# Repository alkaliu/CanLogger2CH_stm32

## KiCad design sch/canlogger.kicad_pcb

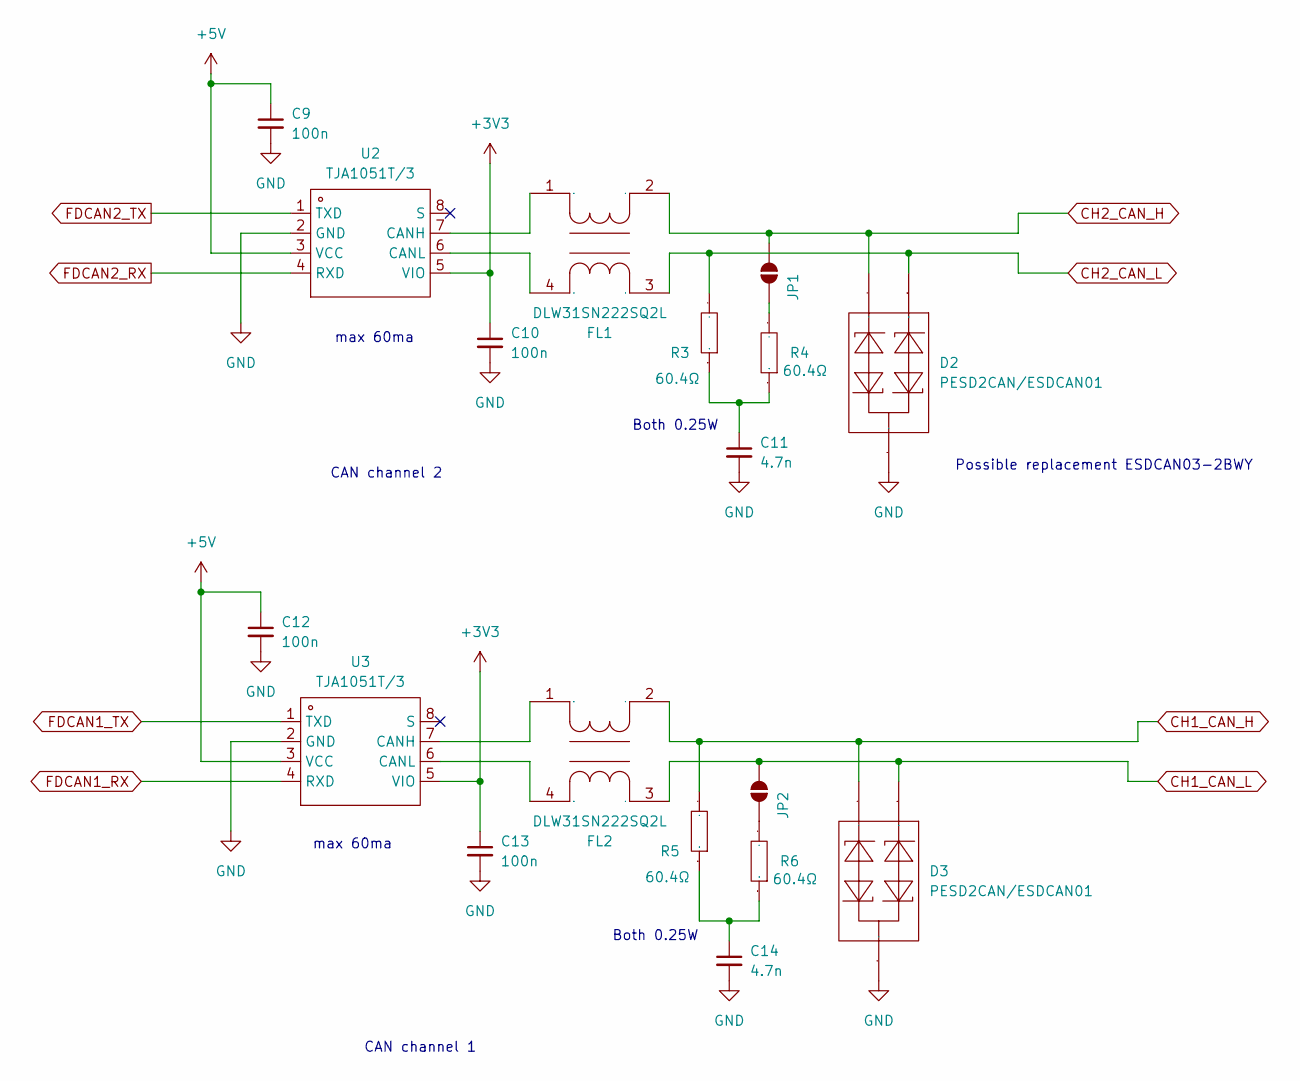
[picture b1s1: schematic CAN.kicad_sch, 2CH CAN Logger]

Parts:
C9, C10, C12, C13: 100n; C0603
C11, C14: 4.7n; C0603
D2, D3: PESD2CAN/ESDCAN01; SOT-23-3_L2.9-W1.3-P1.90-LS2.4-BR; Manufacturer Part PESD2CAN,215; LCSC Part Name 双向ESD 24V截止 峰值脉冲电流：5A@8/20us
FL1, FL2: DLW31SN222SQ2L; FILTER-SMD_4P-L3.2-W1.6-BL_DLW31SN222SQ2L; Manufacturer Part DLW31SN222SQ2L; LCSC Part Name 两路 贴片共模滤波器 阻抗2.2kΩ@100MHz
JP1, JP2: SolderJumper_2_Open; SolderJumper-2_P1.3mm_Open_RoundedPad1.0x1.5mm
R3, R4, R5, R6: 60.4Ω; R1206; Manufacturer Part 1206W4F604JT5E; LCSC Part Name 60.4Ω ±1% 250mW 厚膜电阻
U2, U3: TJA1051T/3; SOIC-8_L4.9-W3.9-P1.27-LS6.0-BL; Manufacturer Part TJA1051T/3/1J; LCSC Part Name TJA1051T/3/1J

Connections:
+3V3: C10.1, C13.1, U2.5 (VIO), U3.5 (VIO); also elsewhere on the board
+5V: C9.1, C12.1, U2.3 (VCC), U3.3 (VCC); also elsewhere on the board
CH1_CAN_H: D3.2, FL2.2, R5.2; also elsewhere on the board
CH1_CAN_L: D3.1, FL2.3, JP2.2 (B); also elsewhere on the board
CH2_CAN_H: D2.2, FL1.2, JP1.2 (B); also elsewhere on the board
CH2_CAN_L: D2.1, FL1.3, R3.2; also elsewhere on the board
FDCAN1_RX: U3.4 (RXD); also elsewhere on the board
FDCAN1_TX: U3.1 (TXD); also elsewhere on the board
FDCAN2_RX: U2.4 (RXD); also elsewhere on the board
FDCAN2_TX: U2.1 (TXD); also elsewhere on the board
GND: C9.2, C10.2, C11.2, C12.2, C13.2, C14.2, D2.3, D3.3, U2.2 (GND), U3.2 (GND); also elsewhere on the board
unnamed: C11.1, R3.1, R4.1
unnamed: C14.1, R5.1, R6.1
unnamed: JP1.1 (A), R4.2
unnamed: JP2.1 (A), R6.2
unnamed: FL1.1, U2.7 (CANH)
unnamed: FL1.4, U2.6 (CANL)
unnamed: FL2.1, U3.7 (CANH)
unnamed: FL2.4, U3.6 (CANL)

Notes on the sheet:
Both 0.25W
max 60ma
CAN channel 2
Possible replacement ESDCAN03-2BWY
CAN channel 1

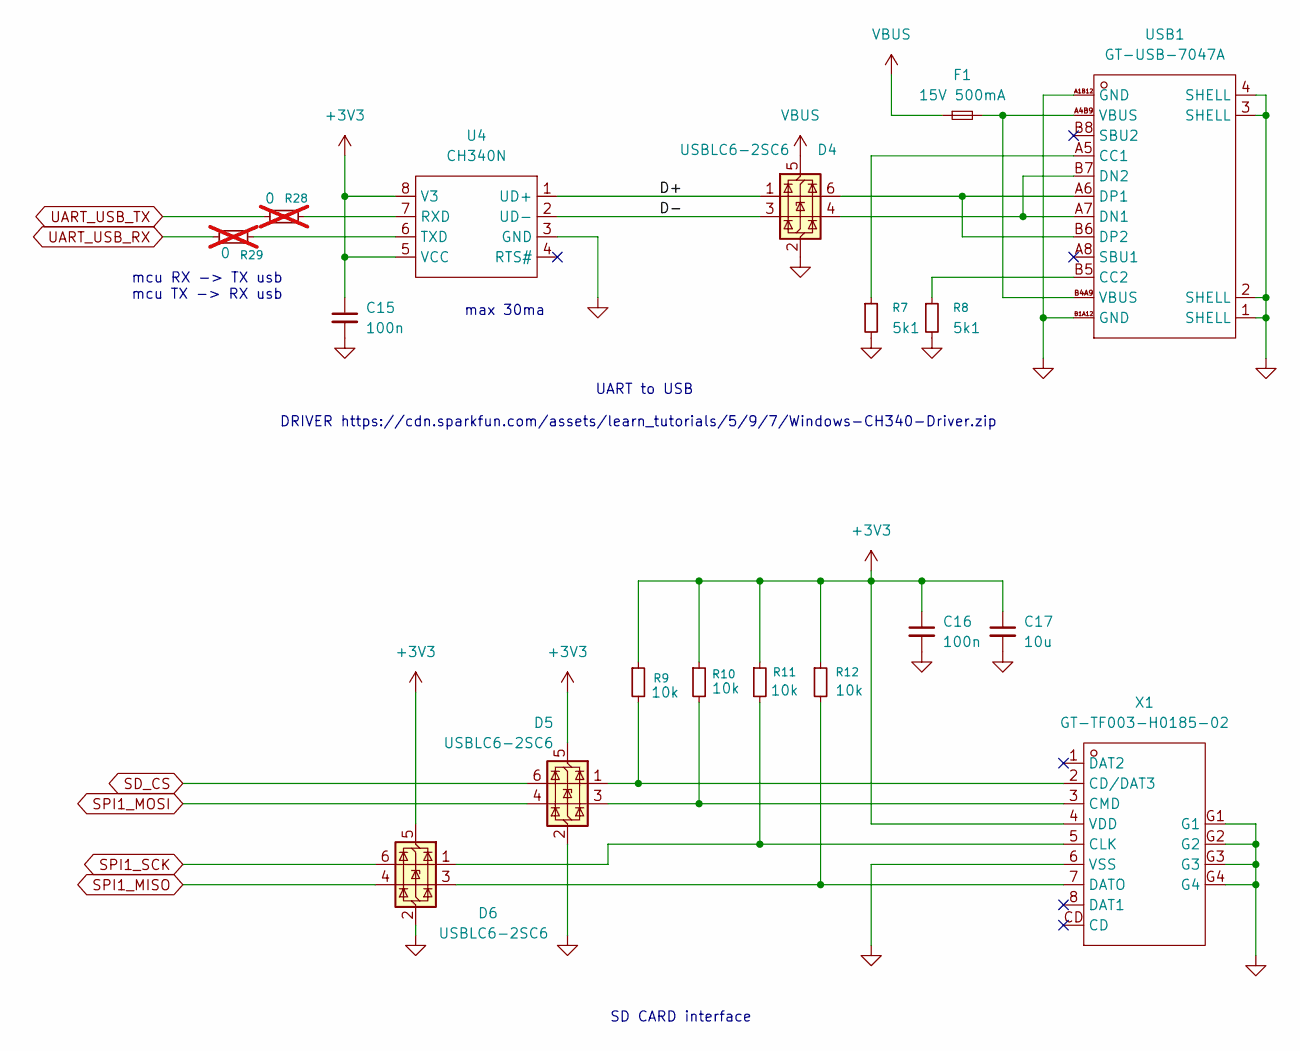
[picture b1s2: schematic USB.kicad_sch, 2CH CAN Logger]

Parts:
C15, C16: 100n; C0603
C17: 10u; C0805
D4, D5, D6: USBLC6-2SC6; SOT-23-6_L2.9-W1.6-P0.95-LS2.8-BL; Manufacturer Part USBLC6-2SC6; LCSC Part Name 单向ESD
F1: 15V 500mA; F1812; Manufacturer Part SMD1812P050TF; LCSC Part Name 15V 500mA 1812自恢复
R7, R8: 5k1; R0603
R9, R10, R11, R12: 10k; R0603
R28, R29: 0; R0603; not fitted
U4: CH340N; SOP-8_L4.9-W3.9-P1.27-LS6.0-BL; Manufacturer Part CH340N; LCSC Part Name USB2.0芯片CH340
USB1: GT-USB-7047A; USB-C-SMD_GT-USB-7047A; Manufacturer Part GT-USB-7047A; LCSC Part Name Type-C 母 卧贴
X1: GT-TF003-H0185-02; SIM-SMD_GT-TF003-H0185-02; Manufacturer Part GT-TF003-H0185-02; LCSC Part Name 自弹式 MicroSD卡(TF卡) 卡座

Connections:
+3V3: C15.1, C16.1, C17.1, D5.5 (VBUS), D6.5 (VBUS), R9.1, R10.1, R11.1, R12.1, U4.5 (VCC), U4.8 (V3), X1.4 (VDD); also elsewhere on the board
/USB_SDCARD/D+: D4.1 (I/O1), U4.1 (UD+)
/USB_SDCARD/D-: D4.3 (I/O2), U4.2 (UD-)
GND: C15.2, C16.2, C17.2, D4.2 (GND), D5.2 (GND), D6.2 (GND), R7.2, R8.2, U4.3 (GND), USB1.1 (SHELL), USB1.2 (SHELL), USB1.3 (SHELL), USB1.4 (SHELL), USB1.A1B12 (GND), USB1.B1A12 (GND), X1.6 (VSS), X1.G1, X1.G2, X1.G3, X1.G4; also elsewhere on the board
unnamed: F1.2, USB1.A4B9 (VBUS), USB1.B4A9 (VBUS)
unnamed: R28.2, U4.7 (RXD)
unnamed: R29.2, U4.6 (TXD)
unnamed: R7.1, USB1.A5 (CC1)
unnamed: R8.1, USB1.B5 (CC2)
unnamed: D4.4 (I/O2), USB1.A7 (DN1), USB1.B7 (DN2)
unnamed: D4.6 (I/O1), USB1.A6 (DP1), USB1.B6 (DP2)
unnamed: D5.1 (I/O1), R9.2, X1.2 (CD/DAT3)
unnamed: D6.1 (I/O1), R11.2, X1.5 (CLK)
unnamed: D5.3 (I/O2), R10.2, X1.3 (CMD)
unnamed: D6.3 (I/O2), R12.2, X1.7 (DATO)
SD_CS: D5.6 (I/O1); also elsewhere on the board
SPI1_MISO: D6.4 (I/O2); also elsewhere on the board
SPI1_MOSI: D5.4 (I/O2); also elsewhere on the board
SPI1_SCK: D6.6 (I/O1); also elsewhere on the board
UART_USB_RX: R29.1; also elsewhere on the board
UART_USB_TX: R28.1; also elsewhere on the board
VBUS: D4.5 (VBUS), F1.1; also elsewhere on the board

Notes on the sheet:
SD CARD interface
DRIVER https://cdn.sparkfun.com/assets/learn_tutorials/5/9/7/Windows-CH340-Driver.zip
max 30ma
mcu RX -> TX usb mcu TX -> RX usb
UART to USB

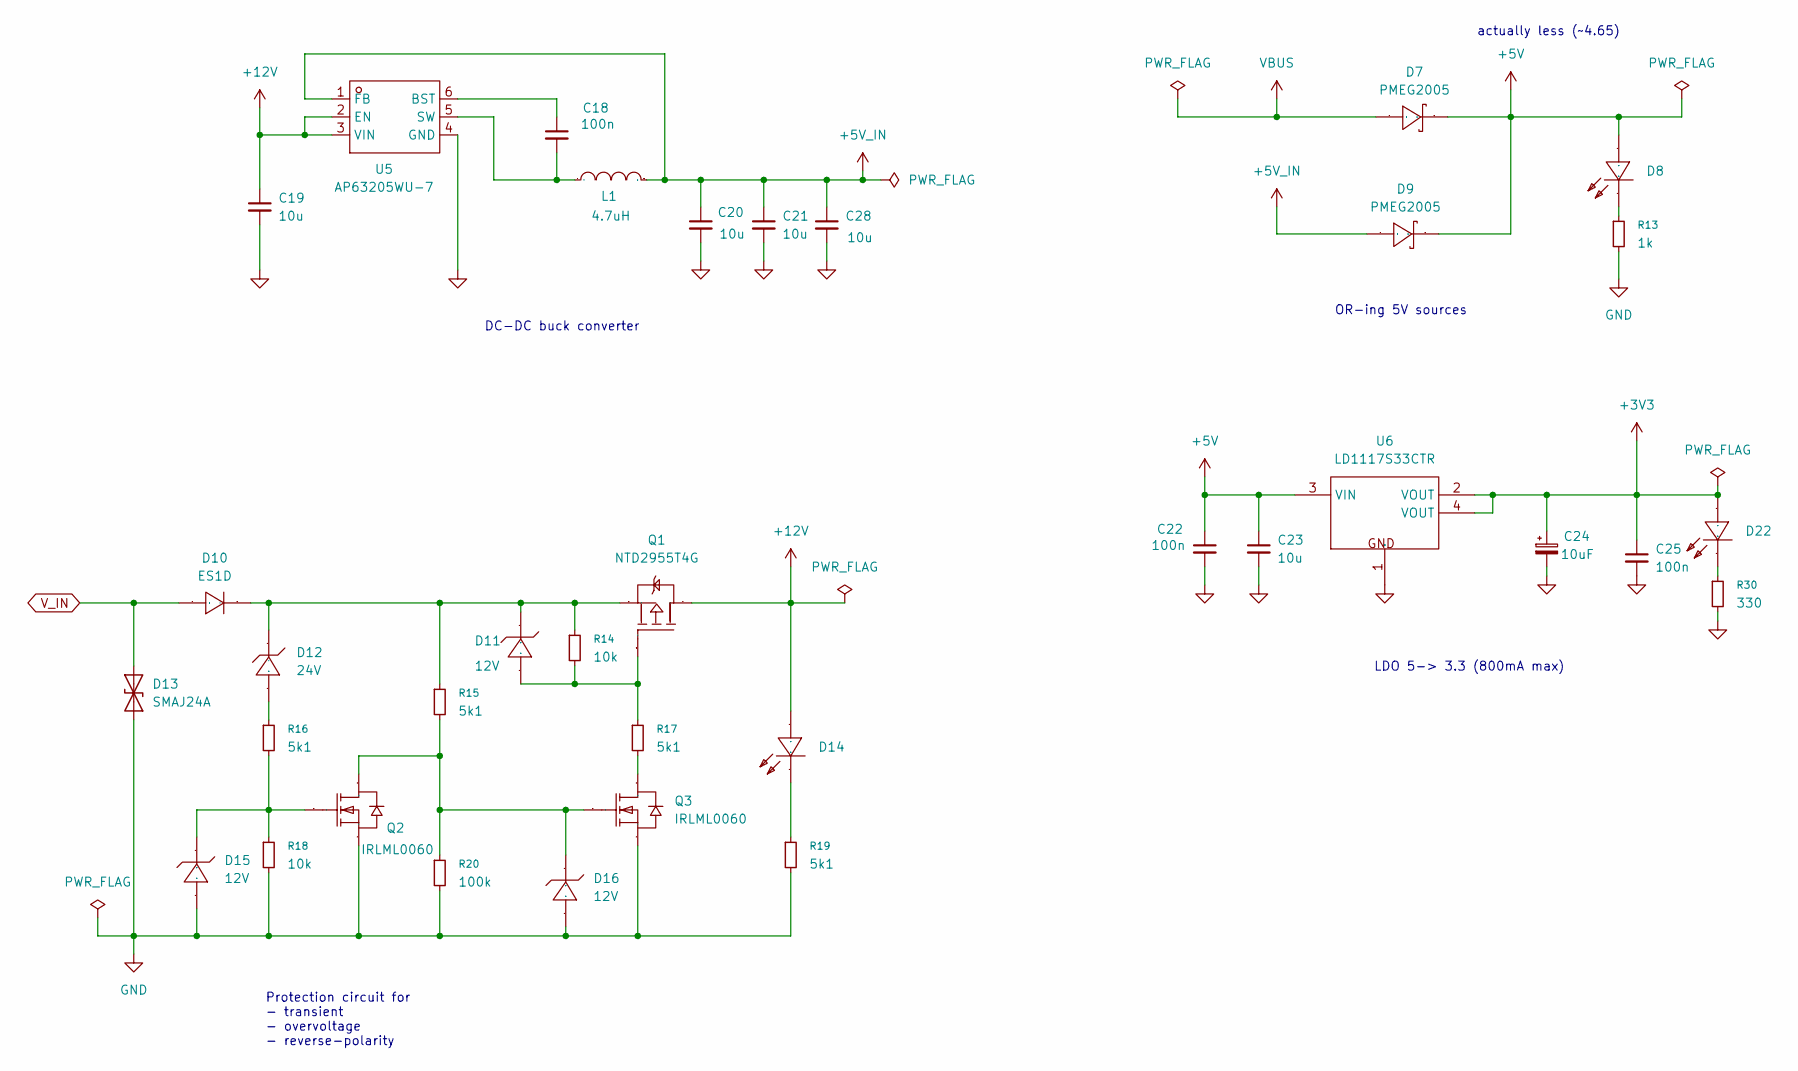
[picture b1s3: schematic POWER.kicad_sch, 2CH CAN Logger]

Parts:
C18, C22, C25: 100n; C0603
C19, C20, C21, C23, C28: 10u; C0805
C24: 10uF; CASE-A_3216; Manufacturer Part TAJA106K010RNJ; LCSC Part Name 10uF ±10% 10V
D7, D9: PMEG2005; SOD-123_L2.8-W1.8-LS3.7-RD; Manufacturer Part PMEG2005EGWX; LCSC Part Name 电压:20V 电流:500mA
D8, D14, D22: LED0603-RD; Manufacturer Part KT-0603R; LCSC Part Name 0603 红灯 高亮
D10: ES1D; SMA_L4.3-W2.6-LS5.2-RD; Manufacturer Part ES1D-E3/61T; LCSC Part Name 耐压:200V 电流:1A 反向恢复时间：15ns
D11, D15, D16: 12V; SOD-123_L2.8-W1.8-LS3.7-RD; Manufacturer Part MMSZ12T1G; LCSC Part Name MMSZ12T1G
D12: 24V; SOD-123_L2.8-W1.8-LS3.7-RD; Manufacturer Part MMSZ5252BT1G; LCSC Part Name MMSZ5252BT1G
D13: SMAJ24A; SMA_L4.4-W2.6-LS5.0-RD; Manufacturer Part SMAJ24A; LCSC Part Name 单向TVS 24V截止 10.3A峰值脉冲
L1: 4.7uH; IND-SMD_L4.4-W4.2-A; Manufacturer Part 0420CDMCCDS-4R7MC; LCSC Part Name 4.7uH ±20% 3A
Q1: NTD2955T4G; TO-252-2_L6.6-W6.1-P4.57-LS9.9-TL-CW; Manufacturer Part NTD2955T4G; LCSC Part Name 1个P沟道 耐压:60V 电流:12A
Q2, Q3: IRLML0060; SOT-23-3_L2.9-W1.6-P1.90-LS2.8-BR; Manufacturer Part IRLML0060TRPBF; LCSC Part Name 1个N沟道 耐压:60V 电流:2.7A
R13: 1k; R0603
R14, R18: 10k; R0603
R15, R16, R17, R19: 5k1; R0603
R20: 100k; R0603
R30: 330; R0603
U5: AP63205WU-7; TSOT-23-6_L2.9-W1.6-P0.95-LS2.8-BL; Manufacturer Part AP63205WU-7; LCSC Part Name 3.8V至32V输入、2A低静态电流同步降压转换器，增强EMI抑制
U6: LD1117S33CTR; SOT-223-4_L6.5-W3.5-P2.30-LS7.0-BR; Manufacturer Part LD1117S33CTR; LCSC Part Name 可调与固定低压降正电压稳压器

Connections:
+3V3: C24.1, C25.1, D22.2 (A), U6.2 (VOUT), U6.4 (VOUT); also elsewhere on the board
+5V: C22.1, C23.1, D7.1 (A), D8.2 (A), D9.1 (A), U6.3 (VIN); also elsewhere on the board
+5V_IN: C20.1, C21.1, C28.1, D9.2 (K), L1.1, U5.1 (FB)
+12V: C19.1, D14.2 (A), Q1.2 (D), U5.2 (EN), U5.3 (VIN)
GND: C19.2, C20.2, C21.2, C22.2, C23.2, C24.2, C25.2, C28.2, D13.2 (A2), D15.2 (A), D16.2 (A), Q2.2 (S), Q3.2 (S), R13.2, R18.2, R19.2, R20.2, R30.2, U5.4 (GND), U6.1 (GND); also elsewhere on the board
unnamed: D8.1 (K), R13.1
unnamed: D10.1 (C), D11.1 (K), D12.1 (C), Q1.3 (S), R14.1, R15.1
unnamed: D11.2 (A), Q1.1 (G), R14.2, R17.1
unnamed: D12.2 (A), R16.1
unnamed: D14.1 (K), R19.1
unnamed: D15.1 (K), Q2.1 (G), R16.2, R18.1
unnamed: D16.1 (K), Q2.3 (D), Q3.1 (G), R15.2, R20.1
unnamed: D22.1 (K), R30.1
unnamed: Q3.3 (D), R17.2
unnamed: C18.1, U5.6 (BST)
unnamed: C18.2, L1.2, U5.5 (SW)
VBUS: D7.2 (K); also elsewhere on the board
V_IN: D10.2 (A), D13.1 (A1); also elsewhere on the board

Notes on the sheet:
LDO 5-> 3.3 (800mA max)
OR-ing 5V sources
DC-DC buck converter
actually less (~4.65)
Protection circuit for - transient - overvoltage - reverse-polarity

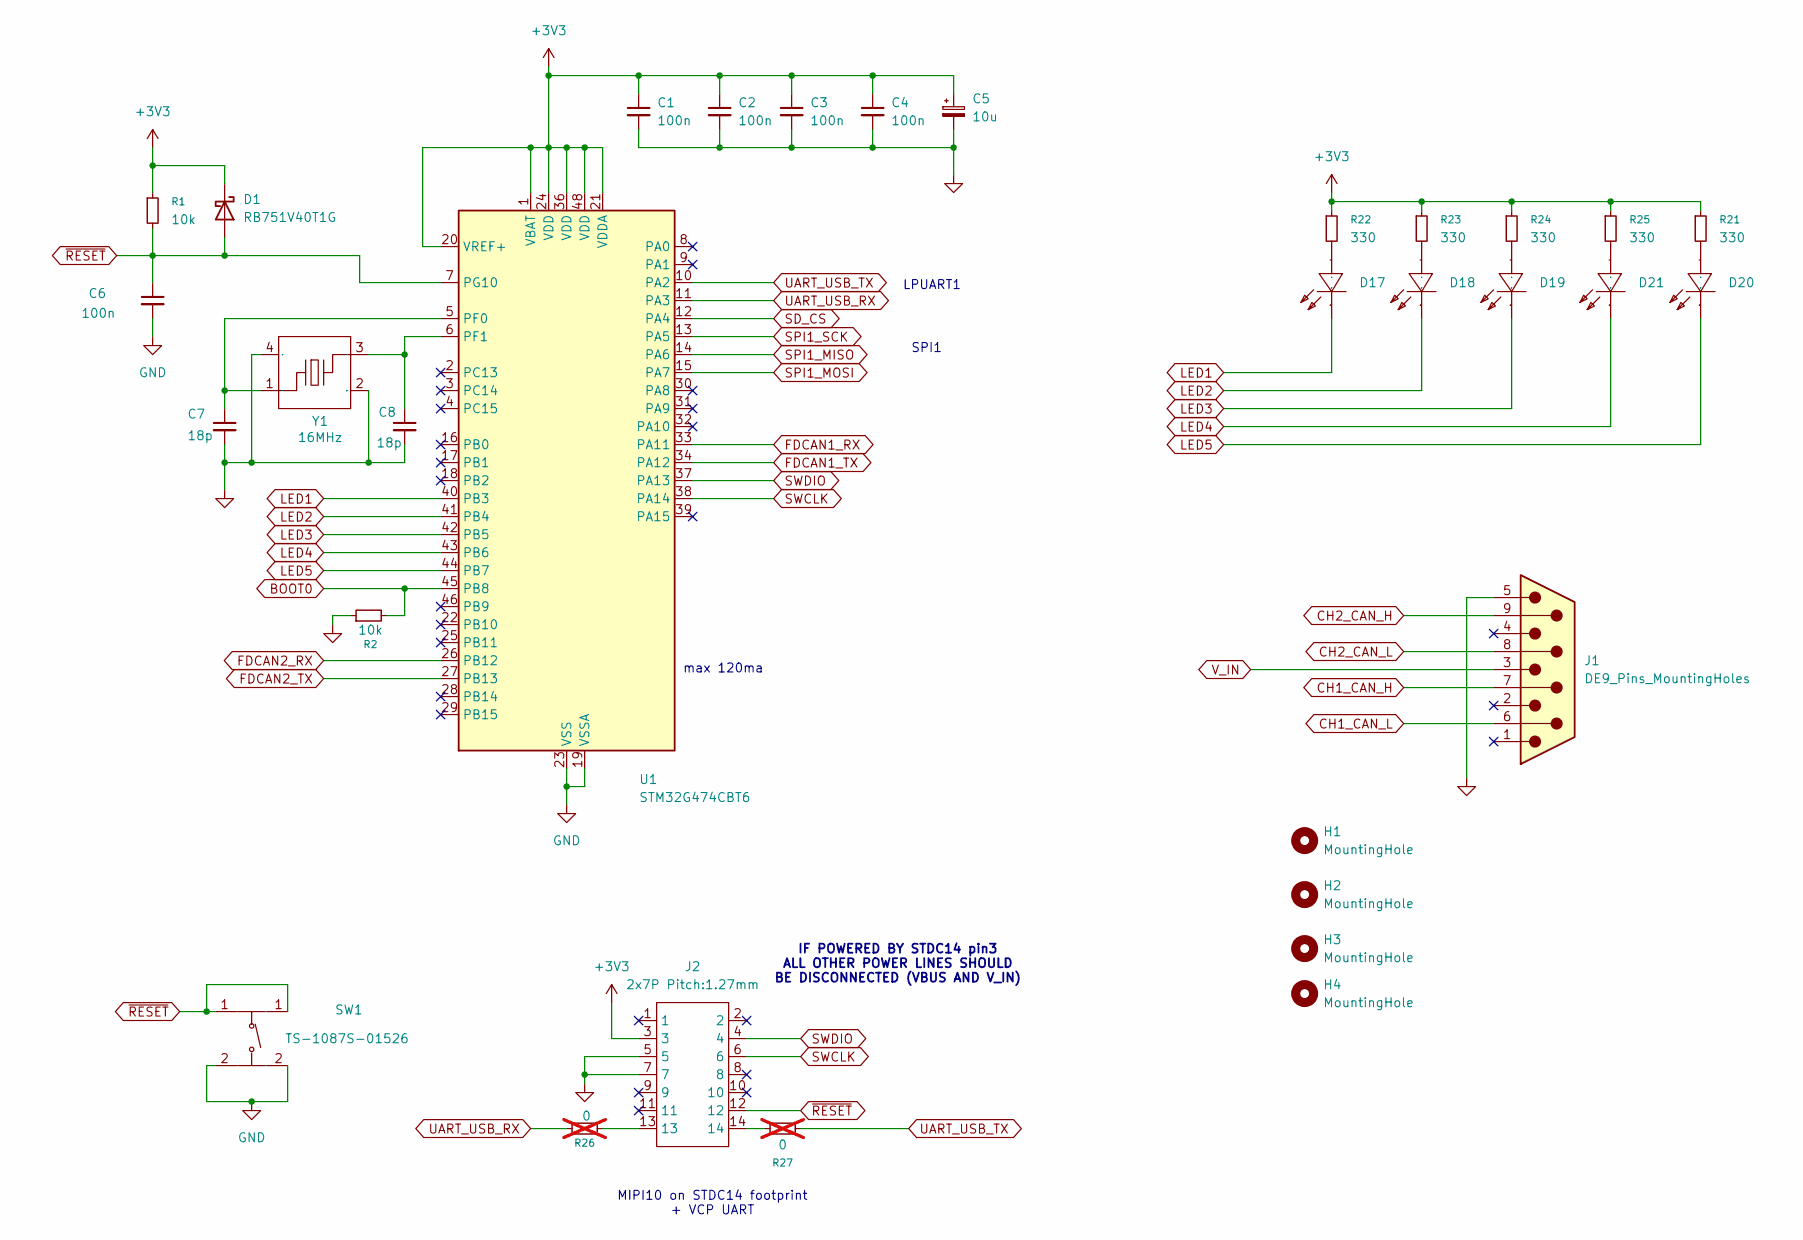
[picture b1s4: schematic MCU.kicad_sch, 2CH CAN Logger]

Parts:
C1, C2, C3, C4, C6: 100n; C0603
C5: 10u; C0805
C7, C8: 18p; C0603
D1: RB751V40T1G; SOD-323_L1.8-W1.3-LS2.5-RD; Manufacturer Part RB751V40T1G; LCSC Part Name 电压:30V 电流:30mA
D17, D18, D19, D20, D21: LED0603-RD; Manufacturer Part KT-0603R; LCSC Part Name 0603 红灯 高亮
H1, H2, H3, H4: MountingHole; MountingHole_2.7mm_M2.5_Pad_TopBottom
J1: DE9_Pins_MountingHoles; DSUB-9_Pins_EdgeMount_P2.77mm
J2: 2x7P Pitch:1.27mm; HDR-SMD_14P-P1.27_HX-PZ1.27-2X7P-TP; Manufacturer Part HX PZ1.27-2x7P TP; LCSC Part Name 2x7P 间距:1.27mm 方针 立贴
R1, R2: 10k; R0603
R21, R22, R23, R24, R25: 330; R0603
R26, R27: 0; R0603; not fitted
SW1: TS-1087S-01526; SW-SMD_L5.2-W5.2-P3.70-LS6.4; Manufacturer Part TS-1087S-01526; LCSC Part Name 5.2*5.2*1.5mm 立贴 轻触开关
U1: STM32G474CBT6; LQFP-48_L7.0-W7.0-P0.50-LS9.0-BL; Manufacturer Part STM32G474CBT6; LCSC Part Name STM32G474CBT6
Y1: 16MHz; CRYSTAL-SMD_4P-L3.2-W2.5-BL_SIT8008BI; Manufacturer Part CF4016M00009001; LCSC Part Name 16MHz ±10ppm 9pF

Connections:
+3V3: C1.1, C2.1, C3.1, C4.1, C5.1, D1.1 (K), J2.3, R1.1, R21.1, R22.1, R23.1, R24.1, R25.1, U1.1 (VBAT), U1.20 (VREF+), U1.21 (VDDA), U1.24 (VDD), U1.36 (VDD), U1.48 (VDD); also elsewhere on the board
BOOT0: R2.2, U1.45 (PB8)
CH1_CAN_H: J1.7; also elsewhere on the board
CH1_CAN_L: J1.6; also elsewhere on the board
CH2_CAN_H: J1.9; also elsewhere on the board
CH2_CAN_L: J1.8; also elsewhere on the board
FDCAN1_RX: U1.33 (PA11); also elsewhere on the board
FDCAN1_TX: U1.34 (PA12); also elsewhere on the board
FDCAN2_RX: U1.26 (PB12); also elsewhere on the board
FDCAN2_TX: U1.27 (PB13); also elsewhere on the board
GND: C1.2, C2.2, C3.2, C4.2, C5.2, C6.2, C7.2, C8.2, J1.5, J2.5, J2.7, R2.1, SW1.2, U1.19 (VSSA), U1.23 (VSS), U1.35 (VSS), U1.47 (VSS), Y1.2 (GND), Y1.4 (GND); also elsewhere on the board
LED1: D17.1 (K), U1.40 (PB3)
LED2: D18.1 (K), U1.41 (PB4)
LED3: D19.1 (K), U1.42 (PB5)
LED4: D21.1 (K), U1.43 (PB6)
LED5: D20.1 (K), U1.44 (PB7)
unnamed: D17.2 (A), R22.2
unnamed: D18.2 (A), R23.2
unnamed: D19.2 (A), R24.2
unnamed: D20.2 (A), R21.2
unnamed: D21.2 (A), R25.2
unnamed: J2.13, R26.2
unnamed: J2.14, R27.1
unnamed: C7.1, U1.5 (PF0), Y1.1
unnamed: C8.1, U1.6 (PF1), Y1.3
SD_CS: U1.12 (PA4); also elsewhere on the board
SPI1_MISO: U1.14 (PA6); also elsewhere on the board
SPI1_MOSI: U1.15 (PA7); also elsewhere on the board
SPI1_SCK: U1.13 (PA5); also elsewhere on the board
SWCLK: J2.6, U1.38 (PA14)
SWDIO: J2.4, U1.37 (PA13)
UART_USB_RX: R26.1, U1.11 (PA3); also elsewhere on the board
UART_USB_TX: R27.2, U1.10 (PA2); also elsewhere on the board
V_IN: J1.3; also elsewhere on the board
~RESET: C6.1, D1.2 (A), J2.12, R1.2, SW1.1, U1.7 (PG10)

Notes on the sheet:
MIPI10 on STDC14 footprint + VCP UART
LPUART1
max 120ma
SPI1
IF POWERED BY STDC14 pin3 ALL OTHER POWER LINES SHOULD BE DISCONNECTED (VBUS AND V_IN)

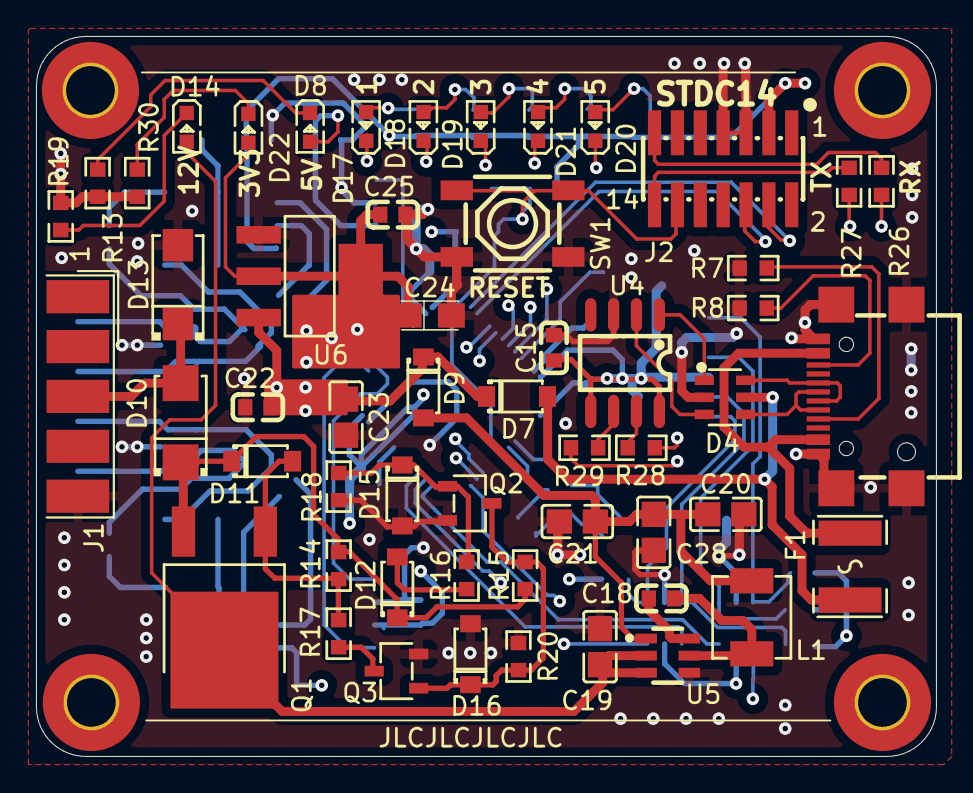
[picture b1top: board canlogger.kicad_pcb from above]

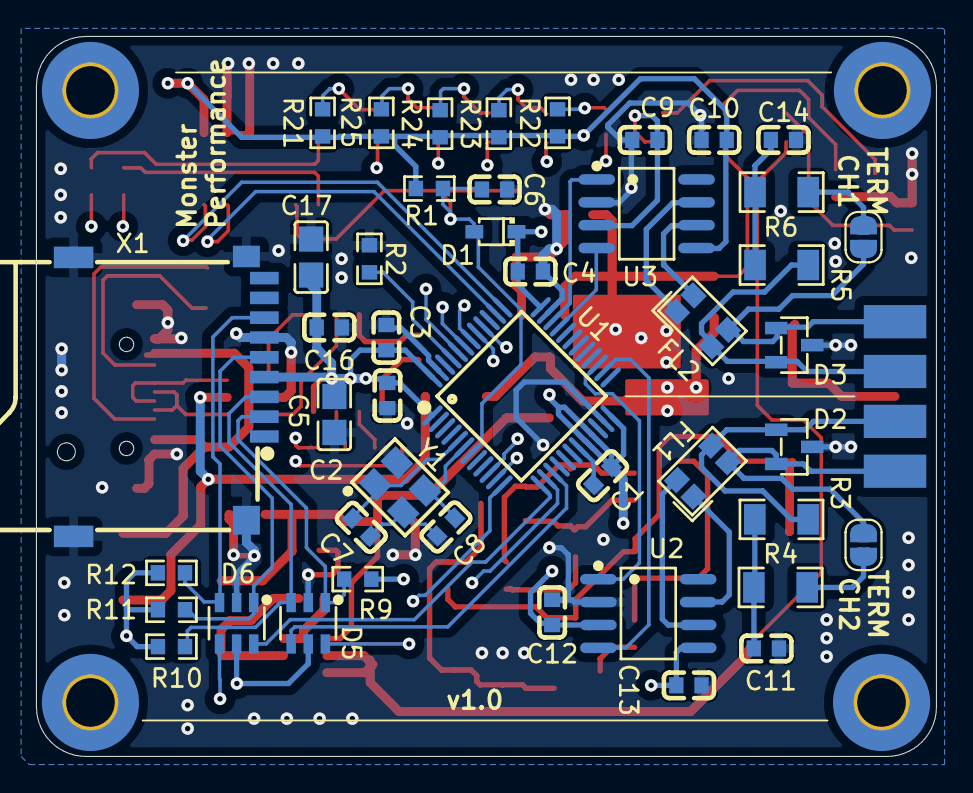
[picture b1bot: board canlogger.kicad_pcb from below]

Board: 4 copper layers, 50.0 x 40.0 mm, 103 parts (45 on the bottom side), 71 nets.

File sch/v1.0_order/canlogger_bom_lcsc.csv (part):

"Reference","Qty","Value","Footprint","Supplier Part","Description"
"C1,C2,C3,C4,C6,C9,C10,C12,C13,C15,C16,C18,C22,C25","14","100n","EasyEDA_Lib:C0603","C14663","Unpolarized capacitor, small symbol"
"C5,C17,C19,C20,C21,C23,C28","7","10u","EasyEDA_Lib:C0805","C15850","Polarized capacitor, small symbol,Unpolarized capacitor, small symbol"
"C7,C8","2","18p","EasyEDA_Lib:C0603","C1647","Unpolarized capacitor, small symbol"
"C11,C14","2","4.7n","EasyEDA_Lib:C0603","C53987","Unpolarized capacitor, small symbol"
"C24","1","10uF","canlogger_custom_lib:CASE-A_3216","C7177","Polarized capacitor, small symbol"
"D1","1","RB751V40T1G","canlogger_custom_lib:SOD-323_L1.8-W1.3-LS2.5-RD","C154819","Schottky diode"
"D2,D3","2","PESD2CAN/ESDCAN01","EasyEDA_Lib:SOT-23-3_L2.9-W1.3-P1.90-LS2.4-BR","C75176","Polarity:Bidirectional Reverse Stand-Off Voltage (Vrwm):24V Clamping Voltage:41V Peak Pulse Current (Ipp):5A@8/20us Peak Pulse Power Dissipation (Ppp):230W@8/20us Voltage - Breakdown:28V Reverse Leakage Current (Ir):1nA Number of Channels:2 Operating Temp"
"D4,D5,D6","3","USBLC6-2SC6","EasyEDA_Lib:SOT-23-6_L2.9-W1.6-P0.95-LS2.8-BL","C7519","Very low capacitance ESD protection diode, 2 data-line, SOT-666"
"D7,D9","2","PMEG2005","EasyEDA_Lib:SOD-123_L2.8-W1.8-LS3.7-RD","C552812","Voltage - Forward(Vf@If):390mV@500mA Voltage - DC Reverse(Vr):20V Current - Rectified:500mA Reverse Leakage Current (Ir):200uA@20V Non-Repetitive Peak Forward Surge Current:10A"
"D8,D14,D17,D18,D19,D20,D21,D22","8","~","EasyEDA_Lib:LED0603-RD","C2286","Emitted Color:Red Power Dissipation:- Forward Current:- Dominant Wavelength:- Dominant Wavelength:- Peak Wavelength:- Diode Configuration:- Lens Color:- Color Temperature:- Color Temperature:- Viewing Angle:- Mounting Sytle:- Operating Temperature:-40°C~+8"
"D10","1","ES1D","canlogger_custom_lib:SMA_L4.3-W2.6-LS5.2-RD","C82648","Voltage - Forward(Vf@If):920mV@1.0A Voltage - DC Reverse(Vr):200V Current - Rectified:1A Reverse Leakage Current (Ir):5uA Reverse Recovery Time (trr):15ns Operating Junction Temperature Range:-55°C~+150°C Operating Junction Temperature Range:-55°C~+150°C Non-"
"D11,D15,D16","3","12V","EasyEDA_Lib:SOD-123_L2.8-W1.8-LS3.7-RD","C72599","Diode Configuration:Independent Zener Voltage(Nom):12V Reverse Leakage Current (Ir):100nA@8V Zener Voltage(Range):11.4V~12.6V Zener Voltage(Range):11.4V~12.6V Pd - Power Dissipation:500mW Impedance(Zzt):25Ω Operating Junction Temperature Range:-55°C~+150°C"
"D12","1","24V","EasyEDA_Lib:SOD-123_L2.8-W1.8-LS3.7-RD","C235986","Diode Configuration:Independent Type Zener Voltage(Nom):24V Reverse Leakage Current (Ir):100nA@18V Zener Voltage(Range):22.8V~25.2V Zener Voltage(Range):22.8V~25.2V Pd - Power Dissipation(Pd):500mW Impedance(Zzt):33Ω"
"D13","1","SMAJ24A","EasyEDA_Lib:SMA_L4.4-W2.6-LS5.0-RD","C148222","400W bidirectional Transient Voltage Suppressor, 24.0Vr, SMA(DO-214AC)"
"F1","1","15V 500mA","EasyEDA_Lib:F1812","C12558","Fuse, small symbol"
"FL1,FL2","2","DLW31SN222SQ2L","canlogger_custom_lib:FILTER-SMD_4P-L3.2-W1.6-BL_DLW31SN222SQ2L","C91594","Number of Lines:2 Voltage Withstand:125V Current Rating:200mA Impedance @ Frequency:2.2kΩ@100MHz Voltage Rating - DC:50V DC Resistance(DCR):1.2Ω Operating Temperature:-40°C~+85°C Operating Temperature:-40°C~+85°C Insulation Resistance(IR):10MΩ"
"J1","1","DE9_Pins_MountingHoles","canlogger_custom_lib:DSUB-9_Pins_EdgeMount_P2.77mm","C75752","9-pin D-SUB connector, pins (male)"
"J2","1","2x7P Pitch:1.27mm","canlogger_custom_lib:HDR-SMD_14P-P1.27_HX-PZ1.27-2X7P-TP","C41376039","Pin Structure:2x7P Pitch:1.27mm Row Spacing:1.27mm Circluar Pins/Square Pins:Pin Header Mounting Type:Surface Mount,Vertical Number of Rows:2 Number of Pins:14P Current Rating:1A Voltage Rating (Max):500V Length of Mating Pin:4mm Insulation Height:1mm Len"
"L1","1","4.7uH","EasyEDA_Lib:IND-SMD_L4.4-W4.2-A","C2638679","Inductance: Tolerance:±20% Tolerance:±20% Rated Current: Saturation Current (Isat):3A DC Resistance (DCR): Type:- Ratings:-"
"Q1","1","NTD2955T4G","EasyEDA_Lib:TO-252-2_L6.6-W6.1-P4.57-LS9.9-TL-CW","C10663","Number:1 piece P-channel Drain to Source Voltage:60V Current - Continuous Drain(Id):12A RDS(on):180mΩ@10V,6A Pd - Power Dissipation:55W Gate Threshold Voltage (Vgs(th)@Id):- Gate Charge(Qg):30nC@10V Input Capacitance(Ciss@Vds):750pF@25V Operating Temperat"
"Q2,Q3","2","IRLML0060","EasyEDA_Lib:SOT-23-3_L2.9-W1.6-P1.90-LS2.8-BR","C67274","Type:1 N-Channel Drain Source Voltage (Vdss): Continuous Drain Current (Id): Drain Source On Resistance (RDS(on)@Vgs,Id):92mΩ@10V Power Dissipation (Pd): Gate Threshold Voltage (Vgs(th)@Id):2.5V@25uA Total Gate Charge (Qg@Vgs):2.5nC Input Capacitance (Cis"
"R1,R2,R9,R10,R11,R12,R14,R18","8","10k","EasyEDA_Lib:R0603","C25804","Resistor, small symbol"
"R3,R4,R5,R6","4","60.4Ω","EasyEDA_Lib:R1206","C57572","Type:Thick Film Resistors Resistance:60.4Ω Tolerance:±1% Tolerance:±1% Power(Watts): Overload Voltage (Max): Temperature Coefficient:±200ppm/°C Temperature Coefficient:±200ppm/°C Operating Temperature Range:-55°C~+155°C Operating Temperature Range:-55°C~+155°C"
"R7,R8,R15,R16,R17,R19","6","5k1","EasyEDA_Lib:R0603","C23186","Resistor, small symbol"
"R13","1","1k","EasyEDA_Lib:R0603","C21190","Resistor, small symbol"
"R20","1","100k","EasyEDA_Lib:R0603","C25803","Resistor, small symbol"
"R21,R22,R23,R24,R25,R30","6","330","EasyEDA_Lib:R0603","C23138","-55℃~+155℃ 100mW 330Ω 75V Thick Film Resistor ±1% ±100ppm/℃ 0603 Chip Resistor - Surface Mount ROHS"
"SW1","1","TS-1087S-01526","EasyEDA_Lib:SW-SMD_L5.2-W5.2-P3.70-LS6.4","C455262","Circuit:SPST Actuator Style:Round Button Mounting Style:Brick nogging Switch Length:5.2mm Switch Width:5.2mm Switch Height:1.5mm Contact Current:50mA Voltage Rating (DC):12V With Lamp:- Mechanical Life:-"
"U1","1","STM32G474CBT6","EasyEDA_Lib:LQFP-48_L7.0-W7.0-P0.50-LS9.0-BL","C730123","STMicroelectronics Arm Cortex-M4 MCU, 512KB flash, 128KB RAM, 170 MHz, 1.71-3.6V, 38 GPIO, LQFP48"
"U2,U3","2","TJA1051T/3","EasyEDA_Lib:SOIC-8_L4.9-W3.9-P1.27-LS6.0-BL","C38695","Type: Data Rate:5Mbps Supply Voltage:4.5V~5.5V Supply Voltage:4.5V~5.5V Supply Current:5mA Operating Temperature:-40°C~+150°C Operating Temperature:-40°C~+150°C"
"U4","1","CH340N","EasyEDA_Lib:SOP-8_L4.9-W3.9-P1.27-LS6.0-BL","C2977777","Applications Function:USB to serial Protocol: Number of Channels:1 Voltage - Supply:3.3V；5V Voltage - Supply:3.3V；5V Data Rate:2Mbps Operating Temperature:-20°C~+70°C Operating Temperature:-20°C~+70°C"
"U5","1","AP63205WU-7","EasyEDA_Lib:TSOT-23-6_L2.9-W1.6-P0.95-LS2.8-BL","C2071056","Function:Buck Voltage - Supply:3.8V~32V Voltage - Supply:3.8V~32V Output Voltage:5V Output Voltage:5V Output Current:2A Frequency - Switching:1.1MHz Frequency - Switching:1.1MHz Operating Temperature:-40°C~+85°C@(TA) Operating Temperature:-40°C~+85°C@(TA) Syn"
"U6","1","LD1117S33CTR","EasyEDA_Lib:SOT-223-4_L6.5-W3.5-P2.30-LS7.0-BR","C35879","Output Type:Fixed Maximum Input Voltage:15V Output Voltage:3.3V Output Voltage:3.3V Output Current:800mA Power Supply Rejection Ratio (PSRR):75dB@(120Hz) Dropout Voltage:1.3V@(800mA) standby current:10mA Feature:Thermal Protection(TSD)；Overcurrent Protect"
"USB1","1","GT-USB-7047A","EasyEDA_Lib:USB-C-SMD_GT-USB-7047A","C963216","Connector Type:Type-C Standard:USB 2.0 Gender:Female Mounting Style:Horizontal attachment Number of Contacts:16P Number of Ports:1 Current Rating - Power (Max):5A Rated Voltage (Max):24V Connect-Disconnect Life:10,000 times Center Height:1.63mm Length:7.3"
"X1","1","GT-TF003-H0185-02","canlogger_custom_lib:SIM-SMD_GT-TF003-H0185-02","C5155564","Card Connection Mode:Push-Push Card Type:MicroSD Card (TF Card) Connector Type:Connector and Ejector Height Above Board:1.85mm Operating Temperature:-40°C~+90°C Operating Temperature:-40°C~+90°C"
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
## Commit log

2025-10-31 Add v1.0 files
2025-11-03 Fix SPI pins add 3.3v led
2025-11-03 change 2x22u to 3x10u plot all order jlcpcb + lcsc
